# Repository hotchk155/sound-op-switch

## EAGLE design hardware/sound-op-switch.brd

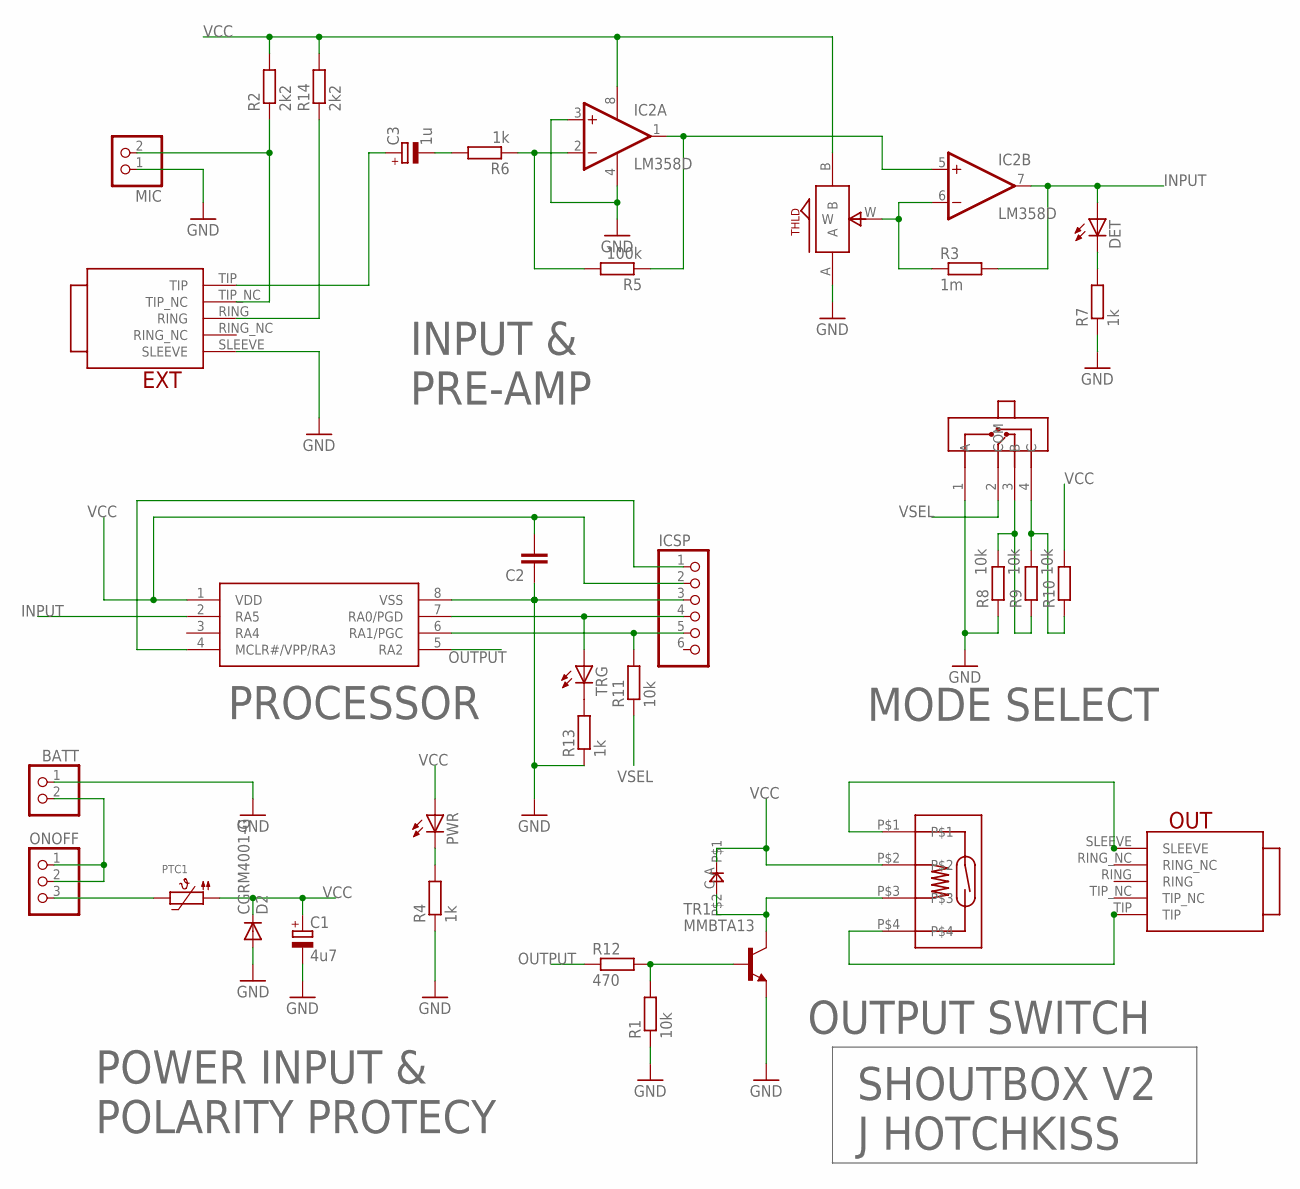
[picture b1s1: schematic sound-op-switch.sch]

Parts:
BATT: PINHD-1X2; 1X02
C1: 4u7; E2,5-6E
C2: C-EUC0805; C0805
C3: 1u; E2,5-6E
D1: 0805DIODE
D2: CGRM4001-G; SOD-123_MINI-SMA
DET: LED3MM
EXT: TRUCONNECTJACK
IC1: PIC12F1822; DIL08
IC2: LM358D; SO08
ICSP: PINHD-1X6; 1X06
MIC: PINHD-1X2; 1X02
ONOFF: PINHD-1X3; 1X03
OUT: TRUCONNECTJACK
PTC1: PTC1206; 1206
PWR: LED3MM
R1, R8, R9, R10, R11: 10k; R0805
R2, R14: 2k2; R0805
R3: 1m; R0805
R4, R6, R7, R13: 1k; R0805
R5: 100k; R0805
R12: 470; R0805
RLY1: 9007-REED-RELAY
SEL: SP4T-SLIDE; SP3T-SLIDE
THLD: ALPS_POT_SMALL; SMALL_ALPS_POT
TR1: MMBTA13; SOT23-BEC
TRG: LED3MM

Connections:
GND: BATT.1, C1.-, C2.1, D2.A, EXT.SLEEVE, IC1.8 (VSS), IC2.3 (+IN), IC2.4 (V-), ICSP.3, MIC.1, R1.1, R4.1, R7.1, R8.1, R13.1, SEL.1 (A), THLD.A, TR1.E
INPUT: DET.A, IC1.2 (RA5), IC2.7 (OUT), R3.2
unnamed: EXT.TIP_NC, MIC.2, R2.1
unnamed: C3.-, R6.2
unnamed: IC2.2 (-IN), R5.2, R6.1
unnamed: DET.K (C), R7.2
unnamed: EXT.RING, R14.1
unnamed: IC1.7 (RA0/PGD), ICSP.4, TRG.A
unnamed: IC2.1 (OUT), IC2.5 (+IN), R5.1
unnamed: R9.2, R10.1, SEL.4 (C)
unnamed: IC1.6 (RA1/PGC), ICSP.5, R11.2
unnamed: R1.2, R12.2, TR1.B
unnamed: IC1.4 (MCLR#/VPP/RA3), ICSP.1
unnamed: C3.+, EXT.TIP
unnamed: IC2.6 (-IN), R3.1, THLD.W
unnamed: R8.2, R9.1, SEL.3 (B)
unnamed: D1.C, RLY1.P$3, TR1.C
unnamed: PWR.K (C), R4.2
unnamed: R13.2, TRG.K (C)
unnamed: BATT.2, ONOFF.1, ONOFF.2
unnamed: ONOFF.3, PTC1.2
unnamed: OUT.SLEEVE, RLY1.P$1
unnamed: OUT.TIP, RLY1.P$4
OUTPUT: IC1.5 (RA2), R12.1
VCC: C1.+, C2.2, D1.A, D2.C, IC1.1 (VDD), IC2.8 (V+), ICSP.2, PTC1.1, PWR.A, R2.2, R10.2, R14.2, RLY1.P$2, THLD.B
VSEL: R11.1, SEL.2 (COM)

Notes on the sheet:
OUTPUT SWITCH
POWER INPUT & POLARITY PROTECY
INPUT & PRE-AMP
PROCESSOR
MODE SELECT
SHOUTBOX V2
J HOTCHKISS

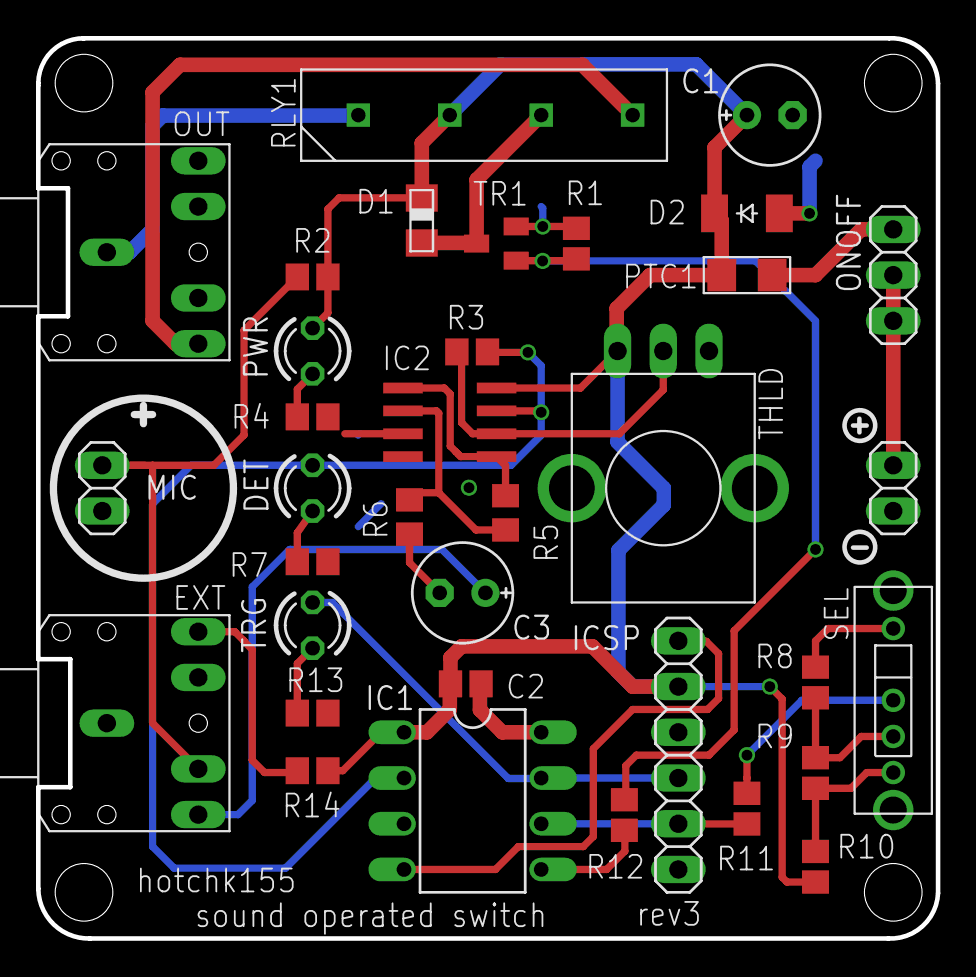
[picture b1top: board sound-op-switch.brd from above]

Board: 2 copper layers, 50.0 x 50.0 mm, 35 parts (0 on the bottom side), 26 nets.

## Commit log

2016-03-05 :boom::camel: Added .gitattributes & .gitignore files
2016-03-05 PCB rev1
2016-03-28 add device names and bom
2016-03-28 case proto
2016-06-13 pcb rev2
2016-06-13 tidy up project
2016-06-13 tidy up again
2016-07-08 REV3
    fix mic position
2016-07-25 case layout for cut
